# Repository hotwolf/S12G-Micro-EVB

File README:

This is the website of the S12G-Micro-EVB project.

...see https://hotwolf.github.io/S12G-Micro-EVB/

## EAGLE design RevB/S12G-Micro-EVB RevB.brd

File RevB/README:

S12G Micro EVB (RevB)
===================== 
Revised version of the S12G-Micro-EVB.

Files:
"S12G-Micro-EVB RevB.sch"               ;Schematic (aEgle 6.2.0)
"S12G-Micro-EVB RevB.brd"               ;PCB layout (Eagle 6.2.0)
"S12G-Micro-EVB RevB Gerber.zip"        ;PCB layout (Gerber)
"S12G-Micro-EVB RevB BOM.txt"           ;Bill of Materials
"S12G-Micro-EVB RevB Schematic.pdf"     ;Schematic
"S12G-Micro-EVB RevB Mounting Plan.pdf" ;Assembly diagram

This work is licensed under a Creative Commons Attribution-ShareAlike 3.0 Unported License (http://creativecommons.org/licenses/by-sa/3.0/).

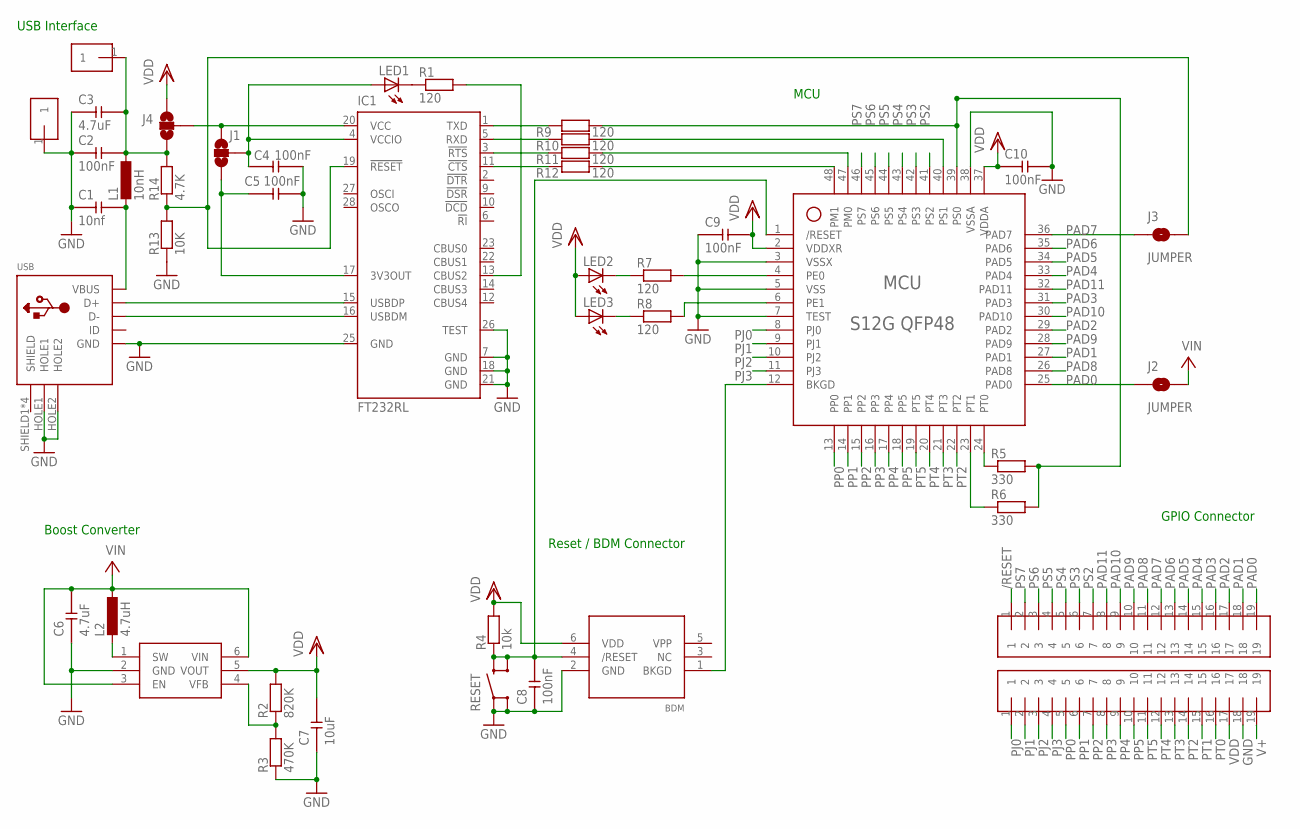
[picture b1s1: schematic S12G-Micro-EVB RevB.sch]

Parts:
BDM: BDM
BOTTOM: 1X19
C1: 10nf; 0805
C2, C4, C5, C8, C9, C10: 100nF; 0805
C3, C6: 4.7uF; 0805
C7: 10uF; 0805
GND: 1X1
IC1: FT232RL; SSOP28
IC2: MCP1640; SOT23-6
J1, J4: JUMPER_2WAY
J2, J3: JUMPER
L1: 10nH; 0805
L2: 4.7uH; LQH3C@1
LED1, LED2, LED3: LED0805; 0805
MCU: S12G QFP48; QFP44
R1, R7, R8, R9, R10, R11, R12: 120; 0805
R2: 820K; 0805
R3: 470K; 0805
R4: 10k; 0805
R5, R6: 330; 0805
R13: 10K; 0805
R14: 4.7K; 0805
RESET: BUTTON
TOP: 1X19
USB: USB; USB_MINI_B
VUSB: 1X1

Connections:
3V3OUT: C5.2, IC1.17 (3V3OUT), J1.3
/RESET: BDM.4 (/RESET), C8.1, MCU.1 (/RESET), R4.2, RESET.2, RESET.4, TOP.1
BKGD: BDM.1 (BKGD), MCU.12 (BKGD)
CBUS2: IC1.13 (CBUS2), R1.1
CTS: MCU.48 (PM1), R12.1
CTS_FT232RL: IC1.11 (!CTS), R12.2
GND: BDM.2 (GND), BOTTOM.18, C1.2, C2.2, C3.2, C4.1, C5.1, C6.2, C7.2, C8.2, C9.2, C10.1, GND.1, IC1.7 (GND), IC1.18 (GND), IC1.21 (GND), IC1.25 (GND), IC1.26 (TEST), IC2.2 (GND), MCU.3 (VSSX), MCU.5 (VSS), MCU.7 (TEST), MCU.38 (VSSA), R3.2, R13.2, RESET.1, RESET.3, USB.GND, USB.HOLE1, USB.HOLE2
unnamed: LED3.2 (C), R8.2
unnamed: IC2.4 (VFB), R2.2, R3.1
unnamed: LED2.2 (C), R7.2
unnamed: IC1.19 (!RESET), J3.2, R13.1, R14.2
unnamed: LED1.2 (C), R1.2
unnamed: IC2.1 (SW), L2.3 (2), L2.4 (2)
PAD0: J2.1, MCU.25 (PAD0), TOP.19
PAD1: MCU.27 (PAD1), TOP.18
PAD2: MCU.29 (PAD2), TOP.17
PAD3: MCU.31 (PAD3), TOP.16
PAD4: MCU.33 (PAD4), TOP.15
PAD5: MCU.34 (PAD5), TOP.14
PAD6: MCU.35 (PAD6), TOP.13
PAD7: J3.1, MCU.36 (PAD7), TOP.12
PAD8: MCU.26 (PAD8), TOP.11
PAD9: MCU.28 (PAD9), TOP.10
PAD10: MCU.30 (PAD10), TOP.9
PAD11: MCU.32 (PAD11), TOP.8
PE0: MCU.4 (PE0), R7.1
PE1: MCU.6 (PE1), R8.1
PJ0: BOTTOM.1, MCU.8 (PJ0)
PJ1: BOTTOM.2, MCU.9 (PJ1)
PJ2: BOTTOM.3, MCU.10 (PJ2)
PJ3: BOTTOM.4, MCU.11 (PJ3)
PP0: BOTTOM.5, MCU.13 (PP0)
PP1: BOTTOM.6, MCU.14 (PP1)
PP2: BOTTOM.7, MCU.15 (PP2)
PP3: BOTTOM.8, MCU.16 (PP3)
PP4: BOTTOM.9, MCU.17 (PP4)
PP5: BOTTOM.10, MCU.18 (PP5)
PS2: MCU.41 (PS2), TOP.7
PS3: MCU.42 (PS3), TOP.6
PS4: MCU.43 (PS4), TOP.5
PS5: MCU.44 (PS5), TOP.4
PS6: MCU.45 (PS6), TOP.3
PS7: MCU.46 (PS7), TOP.2
PT0: BOTTOM.16, MCU.24 (PT0), R5.2
PT1: BOTTOM.15, MCU.23 (PT1), R6.2
PT2: BOTTOM.14, MCU.22 (PT2)
PT3: BOTTOM.13, MCU.21 (PT3)
PT4: BOTTOM.12, MCU.20 (PT4)
PT5: BOTTOM.11, MCU.19 (PT5)
RTS: MCU.47 (PM0), R11.1
RTS_FT232RL: IC1.3 (!RTS), R11.2
RXD: MCU.39 (PS0), R5.1, R6.1, R9.1
RXD_FT232RL: IC1.5 (RXD), R10.2
SHIELD: USB.SHIELD1 (SHIELD), USB.SHIELD2 (SHIELD), USB.SHIELD3 (SHIELD), USB.SHIELD4 (SHIELD)
TXD: MCU.40 (PS1), R10.1
TXD_FT232RL: IC1.1 (TXD), R9.2
USBDN: IC1.16 (USBDM), USB.D-
USBDP: IC1.15 (USBDP), USB.D+
V+: BOTTOM.19, C6.1, IC2.3 (EN), IC2.6 (VIN), J2.2, L2.1, L2.5 (1)
VBUS: C1.1, L1.2, USB.VBUS
VCC: IC1.20 (VCC), J1.1, J4.2
VCCIO: C4.2, IC1.4 (VCCIO), J1.2, LED1.1 (A)
VDD: BDM.6 (VDD), BOTTOM.17, C7.1, C9.1, C10.2, IC2.5 (VOUT), J4.1, LED2.1 (A), LED3.1 (A), MCU.2 (VDDXR), MCU.37 (VDDA), R2.1, R4.1
VDDUSB: C2.1, C3.1, J4.3, L1.1, R14.1, VUSB.1

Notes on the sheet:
Boost Converter
USB Interface
MCU
Reset / BDM Connector
GPIO Connector

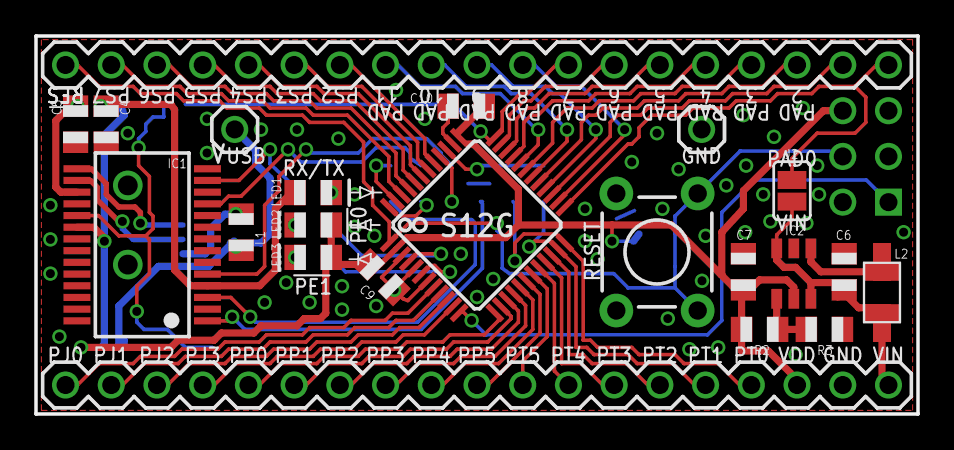
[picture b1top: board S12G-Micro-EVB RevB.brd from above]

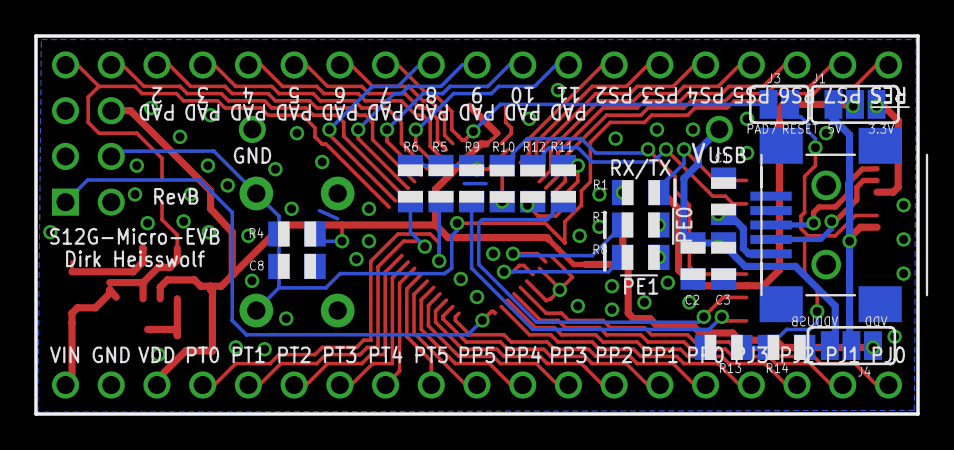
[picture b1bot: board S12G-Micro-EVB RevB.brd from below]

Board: 2 copper layers, 49.0 x 21.0 mm, 43 parts (20 on the bottom side), 64 nets.

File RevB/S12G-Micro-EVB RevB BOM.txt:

Bill of Materials for the S12G-Micro-EVB RevB:
==============================================

ICs:

1x	MC9S12G...LF		LQFP112			MCU
1x	FT232RL			SSOP-28			IC1
1x	MCP1640(C)		SOT23-6			IC2		

Capacitors:

1x	 10nF			0805			C1
6x	100nF			0805			C2, C4, C5, C8, C9, C10 
2x	4.7uF			0805			C3, C6
1x	 10uF			0805			C7


Inductors:

1x	 10nH			0805			L1
1x	4.7uH			LQH3C			L2

Resistors:
5V configuration:

7x	 270			0805			R1, R7, R8, R9, R10, R11, R12
2x	 470			0805			R5, R6, R14
2x  	 10K			0805			R4, 13
1x	220K			0805			R3
1x	680K			0805			R2

3.3V configuration:

7x	 120			0805			R1, R7, R8, R9, R10, R11, R12
2x	 330			0805			R5, R6
1x      4.7K                    0805                    R14
2x	 10K			0805			R4, R13
1x	470K			0805			R3
1x	820K			0805			R2

LEDs:

1x	red			0805			LED_3
1x	green			0805			LED_2
1x	yellow			0805			LED_1

Switch:

1x	button			Print			RESET

Connectors:

1x	USB-Mini-B		SMD			USB
2x	1x19 straight		Print			TOP, BOTTOM
1X	2X3  straight		Print			BDM
2x	1x1  straight		Print			VUSB, GND

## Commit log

2012-03-25 initial release (Rev. A)
2012-03-27 added BOM
2012-03-28 added schematic and mounting plan
2012-04-02 corrected BOM
2012-04-16 fixed BOM
2012-05-25 added Jekyll blog
2012-05-25 fixed link in post
2012-05-25 fixed Atom feed
2012-05-29 fixed wording
2012-06-06 added post
2012-06-06 fixed project names
2013-02-12 renamed atom feed
2014-09-01 started RevB board
2014-09-18 finished RevB layout
2014-09-18 fixed file names
2014-09-18 added Gerber files
2014-09-18 added mounting plan
2014-09-19 added RevB BOM
2014-09-20 updated docs
2014-09-23 new post
2014-11-03 minor fix in BOM files
2016-05-13 fixed layout
2016-05-13 converted textile posts to html
2017-02-24 added TicTacToe project
2018-06-08 updated 404 page
2019-05-30 updated related projects
